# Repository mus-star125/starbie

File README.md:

# ⭐ Starbie

## What's a Starbie and why am I making it?

A Starbie is a mix of a starboy and a Tamagotchi. Basically, it's a little digital pet that you can interact with, but instead of living on your phone, it lives on a PCB!

I'm making Starbie as part of Hack Club's Half Life program, where I get to learn how to design and build my own electronic project from scratch :)))

I chose Starbie because it was the Week 1 guide project for total beginners (like me, **DUHH**). I wanted to challenge myself and learn more about electronics, PCB design, and coding.

## How does it work?

Starbie has a few main components that work together to bring it to life:

- **Microcontroller (XIAO ESP32-C3):** The brain of the project! It runs the code that controls how Starbie behaves.
- **OLED screen:** This is where Starbie's face and expressions appear.
- **Buttons:** These let me interact with Starbie and trigger different actions.
- **DHT11 sensor:** Measures temperature and humidity.
- **MPU6050:** A motion sensor that measures movement and orientation.

All these components connect through a custom-designed PCB (printed circuit board), which I designed using KiCad. The firmware tells the microcontroller what to do, including displaying my custom character on the screen.

## Features!

- **Custom jellyfish sprite:** A pixel-art character designed by me to give Starbie its own personality.
- **OLED display:** Shows Starbie's character and expressions.
- **Button interaction:** Two physical buttons provide inputs for interacting with Starbie.
- **Temperature and humidity sensing:** The DHT11 sensor collects environmental readings.
- **Motion sensing:** The MPU6050 detects movement and orientation.
- **Custom star-shaped PCB:** Designed in KiCad to bring the components together.
- **Custom firmware:** Written for the XIAO ESP32-C3 microcontroller to control the display and device behaviour.

## Software and Tools

- **KiCad:** Schematic capture and PCB design.
- **Arduino IDE:** Firmware development.
- **C++:** Programming the microcontroller.
- **Pixel art:** Designing the custom jellyfish sprite.
- **GitHub:** Storing my project files and documentation.

## Design

### PCB

The PCB has a custom star-shaped outline, with decorative details that give it a playful look while keeping the electronics together on one board.

### Starbie's Character

Meet my custom jellyfish sprite! I designed it in black and white for the OLED display. I plan to experiment with additional expressions and reactions as I develop the firmware.

## Bill of Materials (BOM)

| Part | Qty | Unit Price | Total | Vendor |
|---|---:|---:|---:|---|
| XIAO ESP32-C3 (Main microcontroller) | 1 | $11.61 | $11.61 | [AliExpress](https://www.aliexpress.com/item/1005007378847580.html?mp=1) |
| 0.96-inch I2C OLED Display | 1 | $1.22 | $1.22 | [AliExpress](https://www.aliexpress.com/w/wholesale-0.96-inch-I2C-OLED-display-connector.html) |
| 8-pin Header | 1 | $1.22 | $1.22 | [AliExpress](https://www.aliexpress.com/item/1005012063141186.html) |
| DHT11 Temperature and Humidity Sensor | 1 | $1.22 | $1.22 | [AliExpress](https://www.aliexpress.com/item/1005008953430940.html) |
| Push Button | 1 | $1.22 | $1.22 | [AliExpress](https://www.aliexpress.com/item/1005012448645805.html) |
| 10kΩ Resistor | 1 | $1.22 | $1.22 | [AliExpress](https://www.aliexpress.com/item/1005007539842999.html) |
| MPU6050 Accelerometer and Gyroscope | 1 | $1.22 | $1.22 | [AliExpress](https://www.aliexpress.com/item/1005011826877217.html) |
| Custom PCB | 1 | $11.61 | $11.61 | [JLCPCB](https://cart.jlcpcb.com/shopcart/cart/) |
| **Total** | | | **$26.33** | |

## Final Thoughts & Next Steps

Overall, this has been a really enjoyable project and a good way to test my patience ;) It took me A LOT of time, and my Chromebook kept crashing, but I enjoyed the process.

I learned how to work with KiCad, design a PCB, understand electronic connections, and write firmware for a microcontroller. There were definitely moments when I wanted to give up and restart (and I actually did restart a few times lol), but I learned something new each time.

Thank you to Hack Club and the Half Life community for making this beginner-friendly and giving me the opportunity to try something completely new!

My next step is to get the components, assemble the PCB, and bring Starbie to life.

**Week 1: SUCCESS! ⭐**

## Credits

Built as part of Hack Club's Half Life program. The beginner guide and community helped me get started with my first electronics project.

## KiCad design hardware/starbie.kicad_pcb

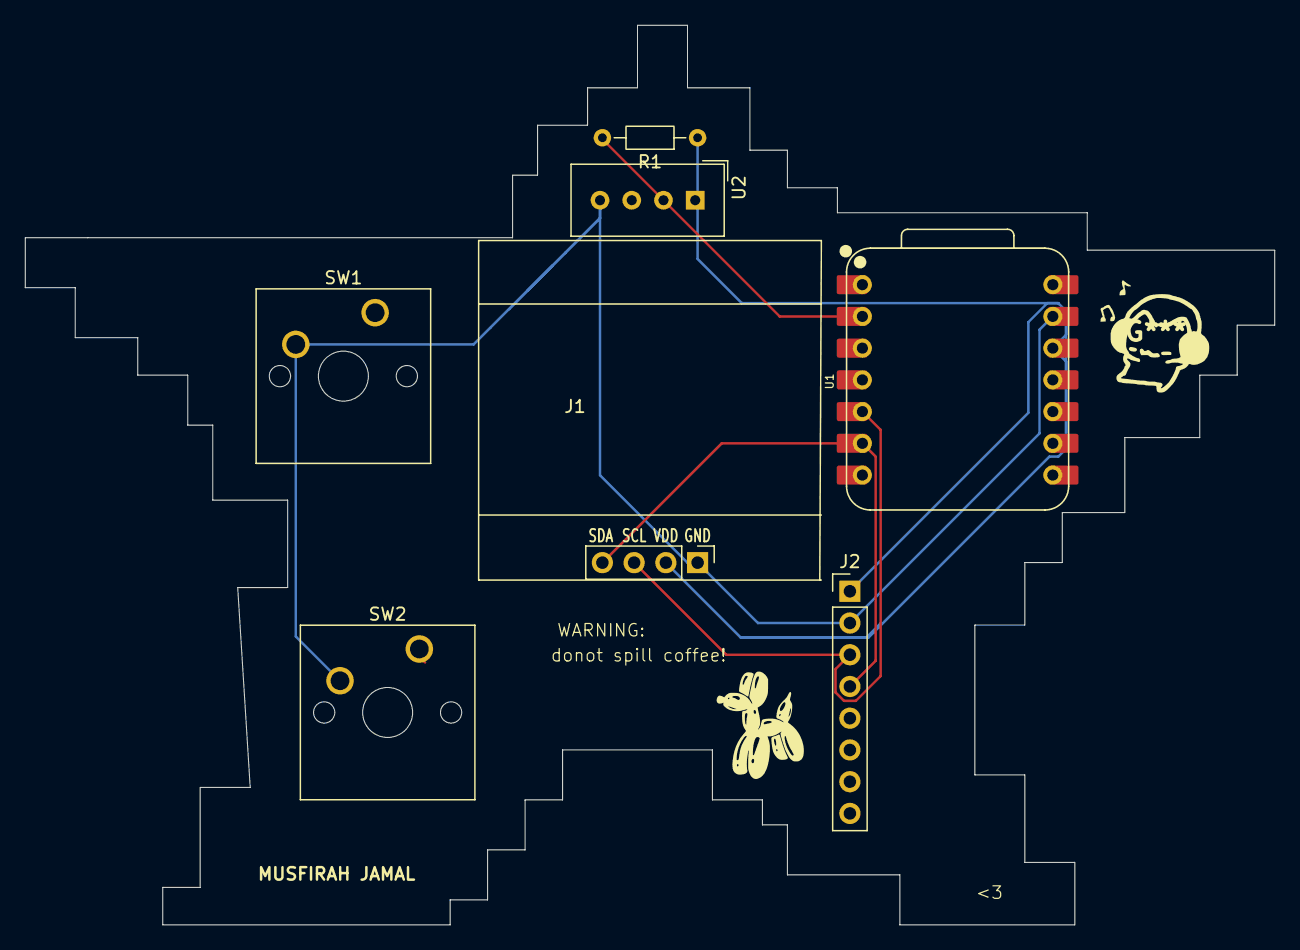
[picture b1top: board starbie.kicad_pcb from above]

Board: 2 copper layers, 100.0 x 72.0 mm, 7 parts (0 on the bottom side), 5 nets.

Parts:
J1: Conn_01x04_Pin; Display_128x64_096_I2C
J2: Conn_01x08_Pin; PinHeader_1x08_P2.54mm_Vertical
R1: 10k; R_Axial_DIN0204_L3.6mm_D1.6mm_P7.62mm_Horizontal
SW1, SW2: SW_Push; SW_Cherry_MX_1.00u_PCB
U1: XIAO-ESP32-C3-SMD; XIAO-ESP32-C6-DIP
U2: DHT11; Aosong_DHT11_5.5x12.0_P2.54mm

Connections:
+3.3V: J1.2, J2.1, R1.1, U1.12 (3V3_OUT), U2.1 (VDD)
/DHT11 DATA: R1.2, U1.2 (D1), U2.2 (DATA)
/SCL: J1.3, J2.3, U1.5 (D4)
/SDA: J1.4, J2.4, U1.6 (D5)
GND: J1.1, J2.2, SW1.2, SW2.2, U1.13 (GND), U2.4 (GND)
